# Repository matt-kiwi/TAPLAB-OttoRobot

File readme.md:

# TAPlab OTTO Robot Inventors Guild 2026

This project is part of the TAPlab NZ [https://www.taplab.nz/](https://www.taplab.nz/)

The young inventors are embarking on creating Otto robots and learning how to code.

The opensource version of OTTO is many years old and based on the Arduino UNO 8 bit micro controller. OTTO is now a commercial product owned by HP [https://hprobots.com/](https://hprobots.com/). The price of the starter kit is beyond what our tamariki can pay, particularly in NZ dollars.

We also believe that the OTTO should be open and available to all students.

*initial PCB design 19th May 2026

9 gram servo with JST-PH 2.0mm connector. This connector style has many advantages over the normal Dupont style connectors, IE not reversible and they lock into place. One challenge is converting a cheap Aliexpress servo to use JST, a local supplier can perform this mod for $1 NZ each.

This is the same conversion HP do on the commercial Otto.

### Otto links

[https://www.ottodiy.com/](https://www.ottodiy.com/) Official Otto website.

[https://github.com/ottodiy](https://github.com/ottodiy) Github page.

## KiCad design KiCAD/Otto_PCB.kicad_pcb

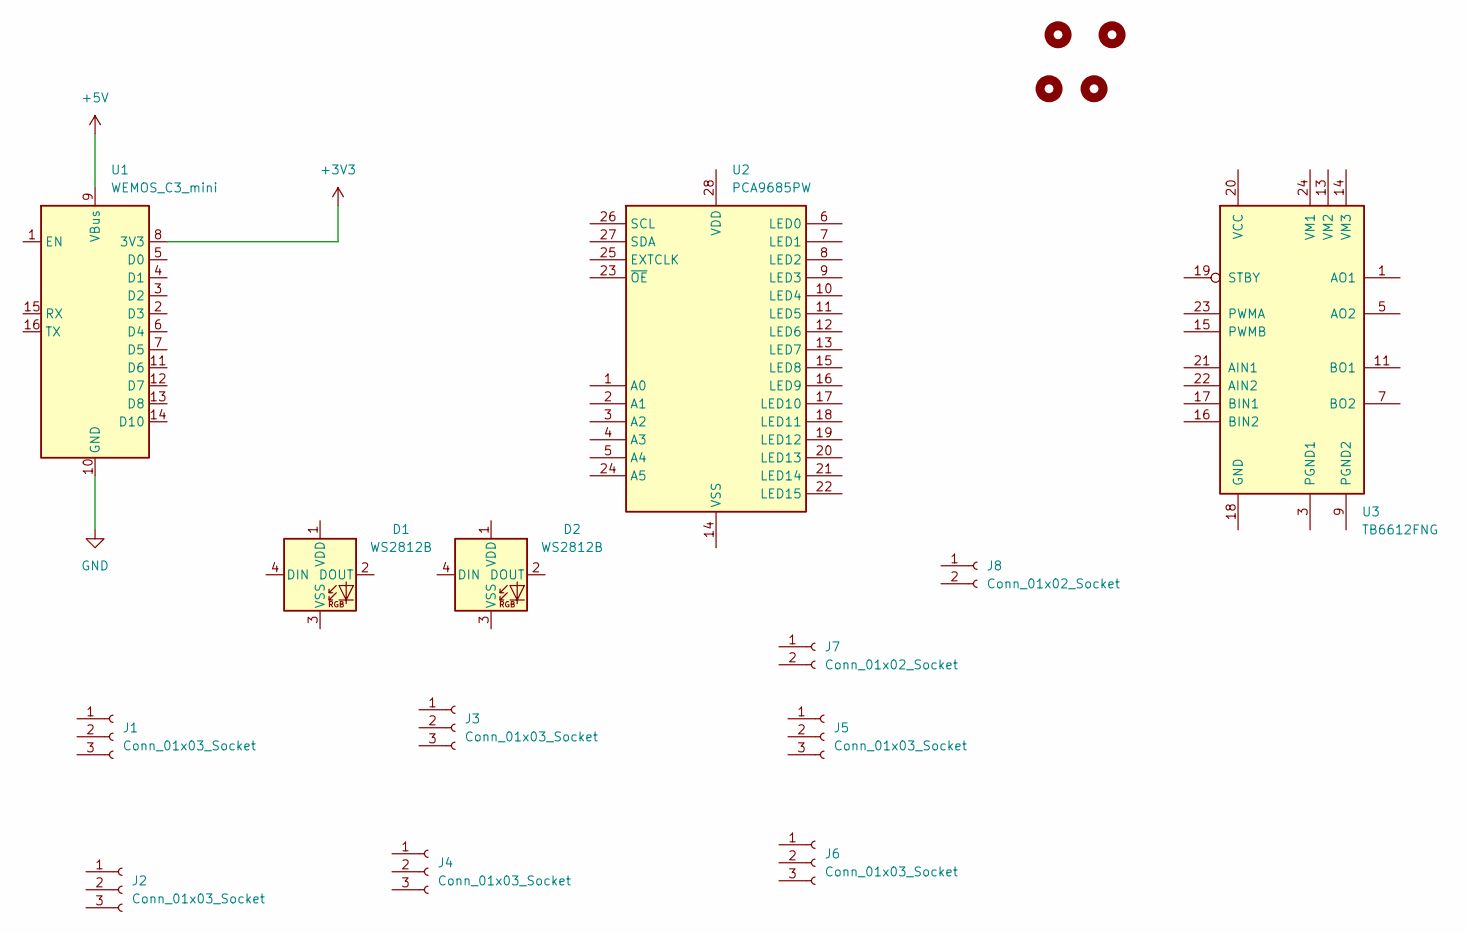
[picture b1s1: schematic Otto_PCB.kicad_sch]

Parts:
D1, D2: WS2812B; LED_WS2812B_PLCC4_5.0x5.0mm_P3.2mm
H1, H2, H3, H4: MountingHole; MountingHole_3.2mm_M3
J1, J2, J3, J4, J5, J6: Conn_01x03_Socket; JST_PH_B3B-PH-SM4-TB_1x03-1MP_P2.00mm_Vertical
J7, J8: Conn_01x02_Socket; JST_PH_B2B-PH-SM4-TB_1x02-1MP_P2.00mm_Vertical
U1: WEMOS_C3_mini; MODULE_ESP32-C3_SUPERMINI_TH
U2: PCA9685PW; TSSOP-28_4.4x9.7mm_P0.65mm
U3: TB6612FNG; TB6612FNG_SSOP-24

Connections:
+3V3: U1.8 (3V3)
+5V: U1.9 (VBus)
GND: U1.10 (GND)
unnamed: U3.1 (AO1), U3.2 (AO1)
unnamed: U3.5 (AO2), U3.6 (AO2)
unnamed: U3.11 (BO1), U3.12 (BO1)
unnamed: U3.7 (BO2), U3.8 (BO2)
unnamed: U3.3 (PGND1), U3.4 (PGND1)
unnamed: U3.9 (PGND2), U3.10 (PGND2)

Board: 2 copper layers, 17 parts (0 on the bottom side), 6 nets, no tracks yet.

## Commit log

2026-05-19 Otto PCB initial commit
2026-05-19 updated readme image
2026-05-19 readme
2026-05-19 web links
2026-05-19 readme servo
